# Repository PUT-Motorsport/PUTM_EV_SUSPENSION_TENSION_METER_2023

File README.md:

# Suspension Tension Meter

This circuit is supposed to measure uniaxial forces acting on the push-rods and send collected data over the CAN bus.

## Build

1. Clone the repository:
    ```
    git clone --recurse-submodules 'https://github.com/PUT-Motorsport/PUTM_EV_SUSPENSION_TENSION_METER_2023.git'
    ```
1. Import the project into the CubeIDE.
1. Temporarily rename `main.cpp` to `main.c`.
1. Run the Device Configuration Tool to update the code.
1. Rename `main.c` back to `main.cpp`.

## Firmware

The [Adafruit library](https://github.com/adafruit/Adafruit_NAU7802) and [this project](https://github.com/alex7709/ECE4180F19_CAN_Project) have been used as a reference for writing the driver for the NAU7802.

## Hardware

- [STM32L4P5RET6](https://www.st.com/resource/en/datasheet/stm32l4p5ae.pdf)
- [NAU7802 24-bit ADC](https://www.nuvoton.com/resource-files/NAU7802%20Data%20Sheet%20V1.7.pdf)
- [EMS20 Shear-web Load Cell](https://www.memidos.com/wp-content/uploads/2022/09/EMS20_en.pdf)

## License

    Copyright 2022 Ignacy Kajdan
    
    Licensed under the Apache License, Version 2.0 (the "License");
    you may not use this file except in compliance with the License.
    You may obtain a copy of the License at
    
      https://www.apache.org/licenses/LICENSE-2.0
    
    Unless required by applicable law or agreed to in writing, software
    distributed under the License is distributed on an "AS IS" BASIS,
    WITHOUT WARRANTIES OR CONDITIONS OF ANY KIND, either express or implied.
    See the License for the specific language governing permissions and
    limitations under the License.

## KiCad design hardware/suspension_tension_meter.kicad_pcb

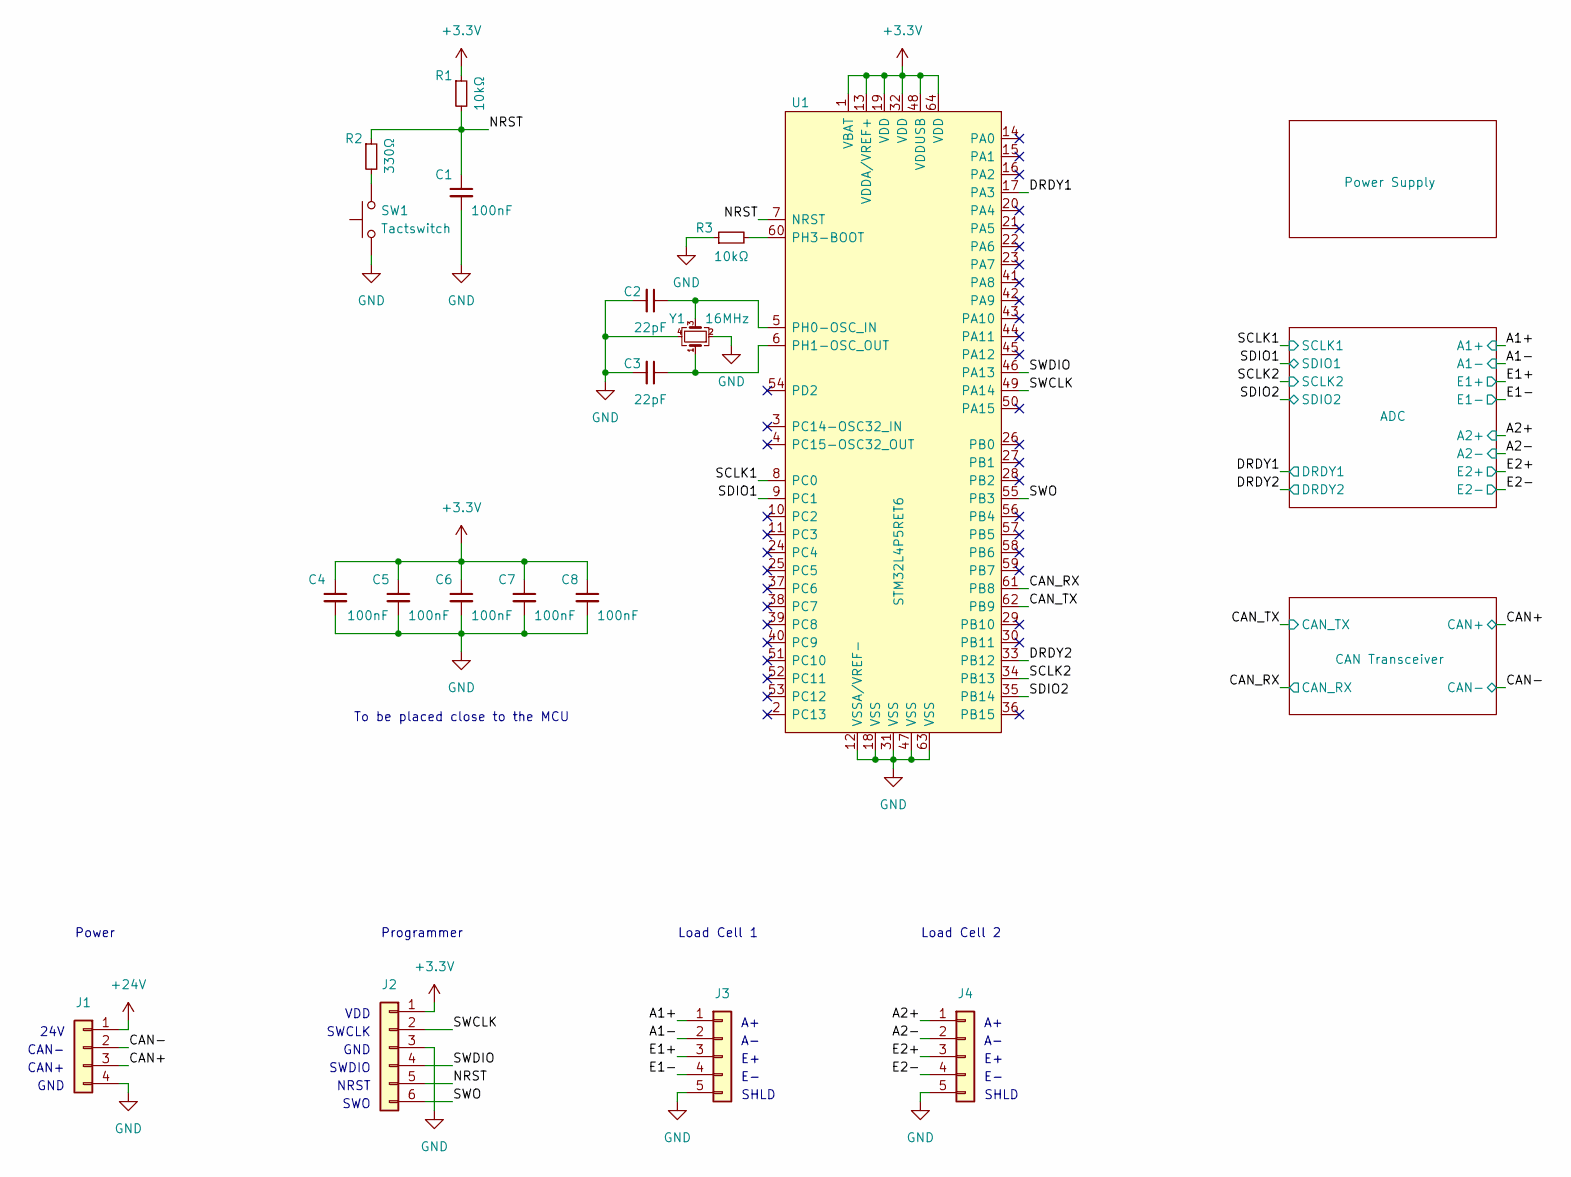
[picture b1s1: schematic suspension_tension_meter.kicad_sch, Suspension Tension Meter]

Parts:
C1, C4, C5, C6, C7, C8: 100nF; C_0603_1608Metric
C2, C3: 22pF; C_0603_1608Metric
J1: Conn_01x04; SolderWire-0.25sqmm_1x04_P4.2mm_D0.65mm_OD1.7mm_Relief
J2: Conn_01x06; PinHeader_1x06_P2.54mm_Vertical
J3, J4: Conn_01x04; Molex_PicoBlade_53048-0510_1x05_P1.25mm_Horizontal
R1, R3: 10kΩ; R_0603_1608Metric
R2: 330Ω; R_0603_1608Metric
SW1: Tactswitch; SW_SPST_PTS645
U1: STM32L4P5RET6; LQFP-64_10x10mm_P0.5mm
Y1: 16MHz; Crystal_SMD_3225-4Pin_3.2x2.5mm

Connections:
+3.3V: C4.1, C5.1, C6.1, C7.1, C8.1, J2.1, J3.3, J4.3, R1.1, U1.1 (VBAT), U1.13 (VDDA/VREF+), U1.19 (VDD), U1.32 (VDD), U1.48 (VDDUSB), U1.64 (VDD); also elsewhere on the board
+24V: J1.1; also elsewhere on the board
/A1+: J3.1; also elsewhere on the board
/A1-: J3.2; also elsewhere on the board
/A2+: J4.1; also elsewhere on the board
/A2-: J4.2; also elsewhere on the board
/CAN+: J1.3; also elsewhere on the board
/CAN-: J1.2; also elsewhere on the board
/CAN_RX: U1.61 (PB8); also elsewhere on the board
/CAN_TX: U1.62 (PB9); also elsewhere on the board
/DRDY1: U1.17 (PA3); also elsewhere on the board
/DRDY2: U1.33 (PB12); also elsewhere on the board
/NRST: C1.1, J2.5, R1.2, R2.1, U1.7 (NRST)
/SCLK1: U1.8 (PC0); also elsewhere on the board
/SCLK2: U1.34 (PB13); also elsewhere on the board
/SDIO1: U1.9 (PC1); also elsewhere on the board
/SDIO2: U1.35 (PB14); also elsewhere on the board
/SWCLK: J2.2, U1.49 (PA14)
/SWDIO: J2.4, U1.46 (PA13)
/SWO: J2.6, U1.55 (PB3)
GND: C1.2, C2.2, C3.2, C4.2, C5.2, C6.2, C7.2, C8.2, J1.4, J2.3, J3.4, J3.5, J4.4, J4.5, R3.1, SW1.1, U1.12 (VSSA/VREF-), U1.18 (VSS), U1.31 (VSS), U1.47 (VSS), U1.63 (VSS), Y1.2, Y1.4; also elsewhere on the board
unnamed: R2.2, SW1.2
unnamed: C2.1, U1.5 (PH0-OSC_IN), Y1.3
unnamed: C3.1, U1.6 (PH1-OSC_OUT), Y1.1
unnamed: R3.2, U1.60 (PH3-BOOT)

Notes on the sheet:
GND
Power
SHLD
To be placed close to the MCU
Load Cell 2
SWCLK
CAN+
NRST
SWO
SHLD
Load Cell 1
CAN-
VDD
Programmer
SWDIO
24V

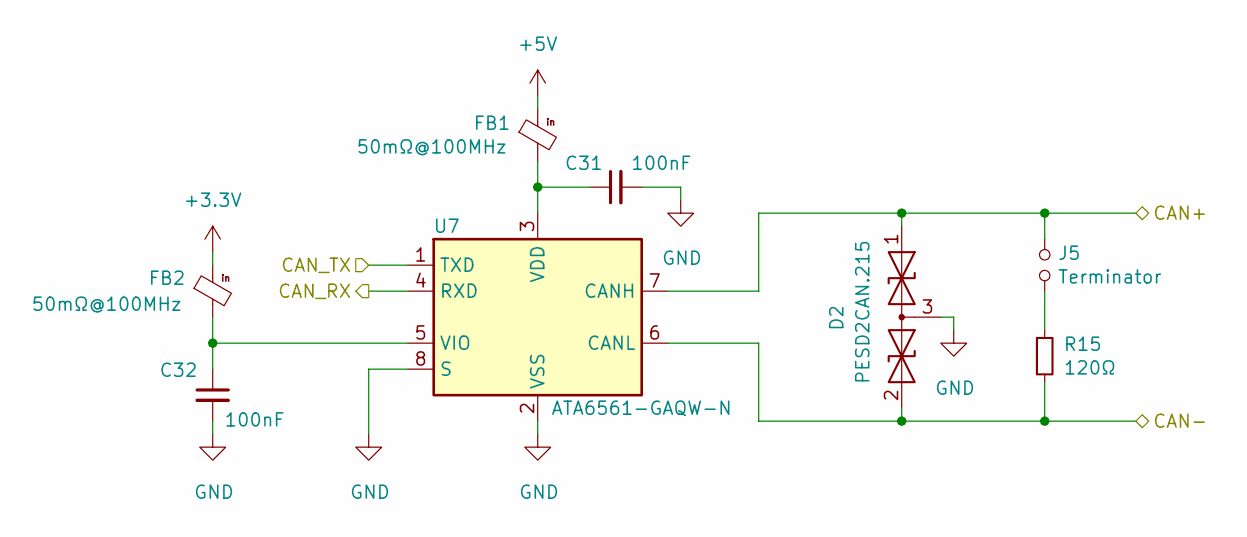
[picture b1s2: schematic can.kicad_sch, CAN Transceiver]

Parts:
C31, C32: 100nF; C_0603_1608Metric
D2: PESD2CAN.215; SOT-23
FB1, FB2: 50mΩ@100MHz; L_1206_3216Metric
J5: Terminator; PinHeader_1x02_P2.54mm_Vertical
R15: 120Ω; R_0603_1608Metric
U7: ATA6561-GAQW-N; SOIC-8_3.9x4.9mm_P1.27mm

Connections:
+3.3V: FB2.1; also elsewhere on the board
+5V: FB1.1; also elsewhere on the board
/CAN+: D2.1 (A1), J5.1, U7.7 (CANH); also elsewhere on the board
/CAN-: D2.2 (A2), R15.2, U7.6 (CANL); also elsewhere on the board
/CAN_RX: U7.4 (RXD); also elsewhere on the board
/CAN_TX: U7.1 (TXD); also elsewhere on the board
GND: C31.2, C32.2, D2.3 (common), U7.2 (VSS), U7.8 (S); also elsewhere on the board
unnamed: J5.2, R15.1
unnamed: C31.1, FB1.2, U7.3 (VDD)
unnamed: C32.1, FB2.2, U7.5 (VIO)

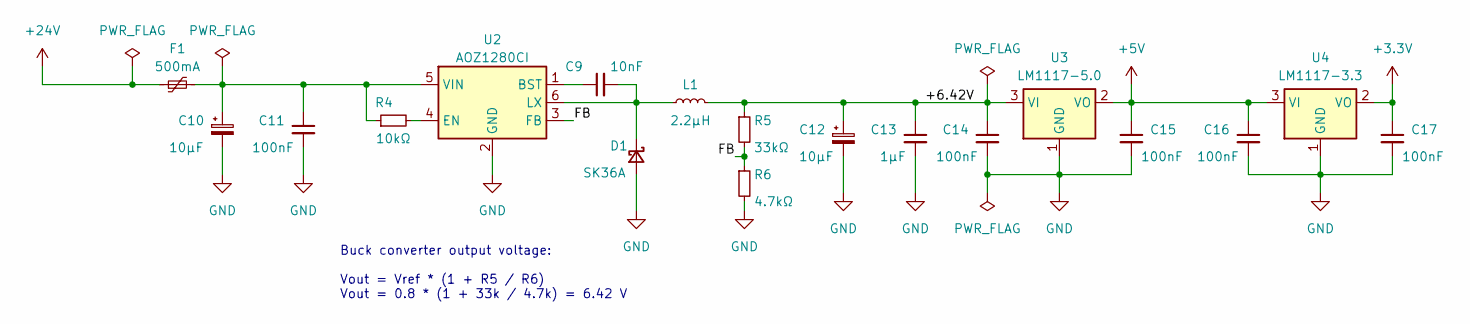
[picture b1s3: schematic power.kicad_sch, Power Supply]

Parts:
C9: 10nF; C_0603_1608Metric
C10, C12: 10μF; CP_Elec_6.3x5.4
C11, C14, C15, C16, C17: 100nF; C_0603_1608Metric
C13: 1μF; C_0603_1608Metric
D1: SK36A; D_SMA
F1: 500mA; Fuse_0805_2012Metric
L1: 2.2μH; L_Bourns-SRN4018
R4: 10kΩ; R_0603_1608Metric
R5: 33kΩ; R_0603_1608Metric
R6: 4.7kΩ; R_0603_1608Metric
U2: AOZ1280CI; SOT-23-6
U3: LM1117-5.0; SOT-223-3_TabPin2
U4: LM1117-3.3; SOT-223-3_TabPin2

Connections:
+3.3V: C17.1, U4.2 (VO); also elsewhere on the board
+5V: C15.1, C16.1, U3.2 (VO), U4.3 (VI); also elsewhere on the board
+24V: F1.1; also elsewhere on the board
/Power Supply/+6.42V: C12.1, C13.1, C14.1, L1.2, R5.1, U3.3 (VI)
/Power Supply/FB: R5.2, R6.1, U2.3 (FB)
GND: C10.2, C11.2, C12.2, C13.2, C14.2, C15.2, C16.2, C17.2, D1.2 (A), R6.2, U2.2 (GND), U3.1 (GND), U4.1 (GND); also elsewhere on the board
unnamed: C10.1, C11.1, F1.2, R4.1, U2.5 (VIN)
unnamed: C9.2, D1.1 (K), L1.1, U2.6 (LX)
unnamed: C9.1, U2.1 (BST)
unnamed: R4.2, U2.4 (EN)

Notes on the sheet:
Buck converter output voltage: Vout = Vref * (1 + R5 / R6) Vout = 0.8 * (1 + 33k / 4.7k) = 6.42 V

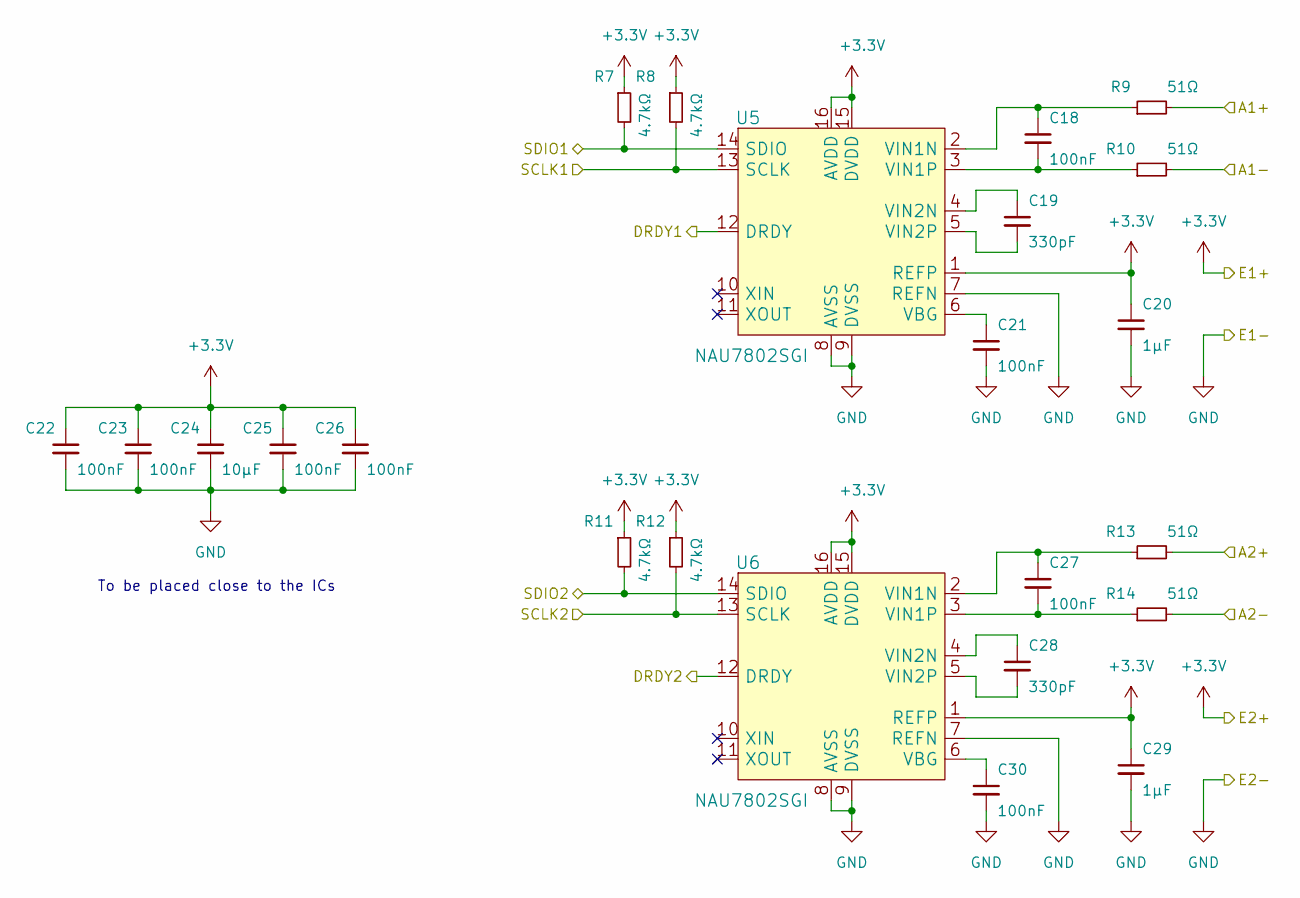
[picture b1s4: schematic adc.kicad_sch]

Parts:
C18, C21, C22, C23, C25, C26, C27, C30: 100nF; C_0603_1608Metric
C19, C28: 330pF; C_0603_1608Metric
C20, C29: 1μF; C_0603_1608Metric
C24: 10μF; C_0603_1608Metric
R7, R8, R11, R12: 4.7kΩ; R_0603_1608Metric
R9, R10, R13, R14: 51Ω; R_0603_1608Metric
U5, U6: NAU7802SGI; SOIC-16_3.9x9.9mm_P1.27mm

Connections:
+3.3V: C20.1, C22.1, C23.1, C24.1, C25.1, C26.1, C29.1, R7.1, R8.1, R11.1, R12.1, U5.1 (REFP), U5.15 (DVDD), U5.16 (AVDD), U6.1 (REFP), U6.15 (DVDD), U6.16 (AVDD); also elsewhere on the board
/A1+: R9.2; also elsewhere on the board
/A1-: R10.2; also elsewhere on the board
/A2+: R13.2; also elsewhere on the board
/A2-: R14.2; also elsewhere on the board
/DRDY1: U5.12 (DRDY); also elsewhere on the board
/DRDY2: U6.12 (DRDY); also elsewhere on the board
/SCLK1: R8.2, U5.13 (SCLK); also elsewhere on the board
/SCLK2: R12.2, U6.13 (SCLK); also elsewhere on the board
/SDIO1: R7.2, U5.14 (SDIO); also elsewhere on the board
/SDIO2: R11.2, U6.14 (SDIO); also elsewhere on the board
GND: C20.2, C21.2, C22.2, C23.2, C24.2, C25.2, C26.2, C29.2, C30.2, U5.7 (REFN), U5.8 (AVSS), U5.9 (DVSS), U6.7 (REFN), U6.8 (AVSS), U6.9 (DVSS); also elsewhere on the board
unnamed: C21.1, U5.6 (VBG)
unnamed: C18.1, R9.1, U5.2 (VIN1N)
unnamed: C18.2, R10.1, U5.3 (VIN1P)
unnamed: C19.1, U5.4 (VIN2N)
unnamed: C19.2, U5.5 (VIN2P)
unnamed: C30.1, U6.6 (VBG)
unnamed: C27.1, R13.1, U6.2 (VIN1N)
unnamed: C27.2, R14.1, U6.3 (VIN1P)
unnamed: C28.1, U6.4 (VIN2N)
unnamed: C28.2, U6.5 (VIN2P)

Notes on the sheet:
To be placed close to the ICs

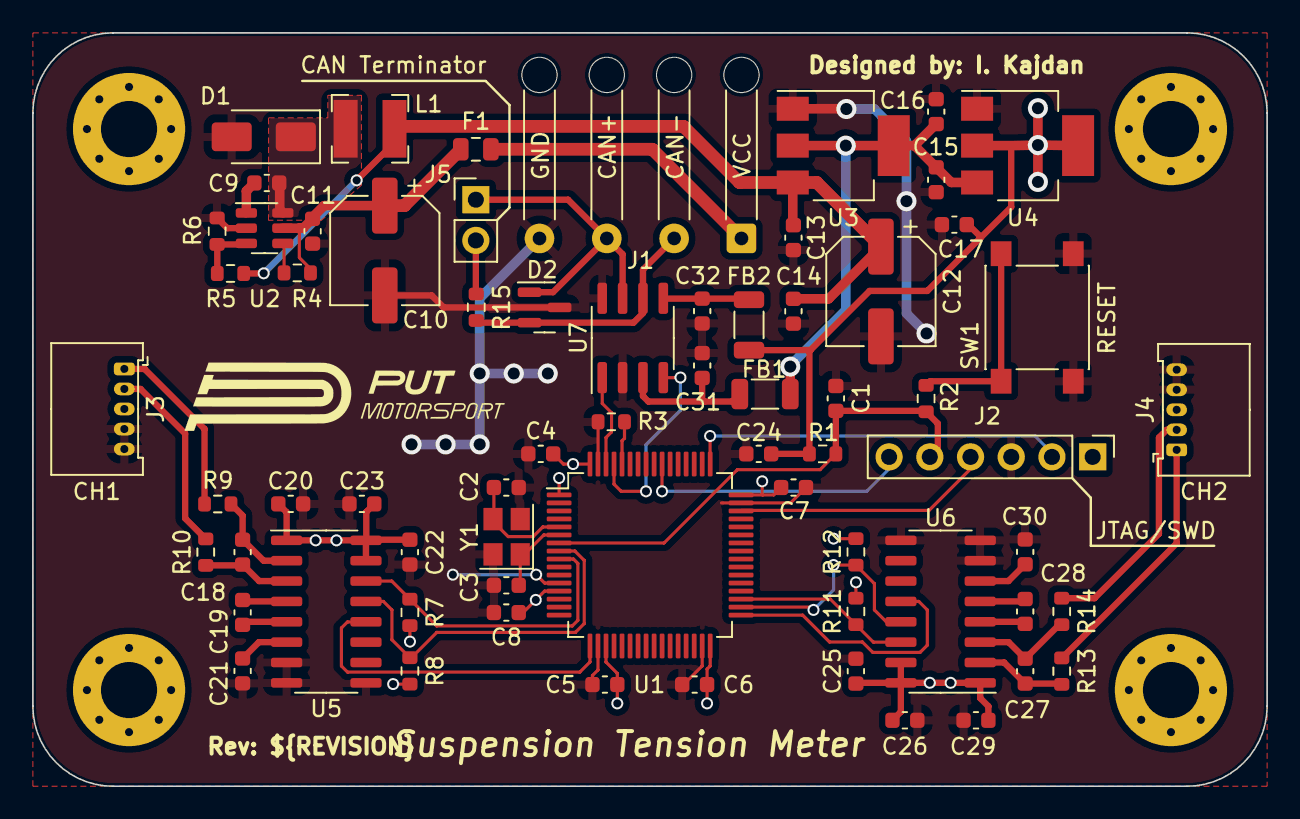
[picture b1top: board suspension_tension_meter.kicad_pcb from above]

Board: 2 copper layers, 77.0 x 47.0 mm, 67 parts (0 on the bottom side), 45 nets.

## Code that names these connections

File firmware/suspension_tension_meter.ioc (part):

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Mcu.Name=STM32L4P5R(G-E)Tx
Mcu.Package=LQFP64
Mcu.UserName=STM32L4P5RETx
PA13\ (JTMS/SWDIO).GPIOParameters=GPIO_Label
PA13\ (JTMS/SWDIO).GPIO_Label=SWDIO
PA13\ (JTMS/SWDIO).Signal=SYS_JTMS-SWDIO
PA14\ (JTCK/SWCLK).GPIOParameters=GPIO_Label
PA14\ (JTCK/SWCLK).GPIO_Label=SWCLK
PA14\ (JTCK/SWCLK).Signal=SYS_JTCK-SWCLK
PA3.GPIOParameters=GPIO_Label
PA3.GPIO_Label=DRDY1
PA3.Signal=GPXTI3
PB12.GPIOParameters=GPIO_Label
PB12.GPIO_Label=DRDY2
PB12.Signal=GPXTI12
PB13.GPIOParameters=GPIO_Label
PB13.GPIO_Label=SCLK2
PB13.Mode=I2C
PB13.Signal=I2C2_SCL
PB14.GPIOParameters=GPIO_Label
PB14.GPIO_Label=SDIO2
PB14.Mode=I2C
PB14.Signal=I2C2_SDA
PB3\ (JTDO/TRACESWO).GPIOParameters=GPIO_Label
PB3\ (JTDO/TRACESWO).GPIO_Label=SWO
PB3\ (JTDO/TRACESWO).Signal=SYS_JTDO-SWO
PB8.GPIOParameters=GPIO_Label
PB8.GPIO_Label=CAN_RX
PB8.Mode=CAN_Activate
PB8.Signal=CAN1_RX
PB9.GPIOParameters=GPIO_Label
PB9.GPIO_Label=CAN_TX
PB9.Mode=CAN_Activate
PB9.Signal=CAN1_TX
PC0.GPIOParameters=GPIO_Label
PC0.GPIO_Label=SCLK1
PC0.Mode=I2C
PC0.Signal=I2C3_SCL
PC1.GPIOParameters=GPIO_Label
PC1.GPIO_Label=SDIO1
PC1.Mode=I2C
PC1.Signal=I2C3_SDA
PH0-OSC_IN\ (PH0).Mode=HSE-External-Oscillator
PH0-OSC_IN\ (PH0).Signal=RCC_OSC_IN
PH1-OSC_OUT\ (PH1).Mode=HSE-External-Oscillator
PH1-OSC_OUT\ (PH1).Signal=RCC_OSC_OUT
RCC.HSE_VALUE=8000000
RCC.SYSCLKFreq_VALUE=64000000
RCC.SYSCLKSource=RCC_SYSCLKSOURCE_PLLCLK
board=custom

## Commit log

2022-11-21 Improve the CAN transceiver circuit
2022-11-21 Add a low-pass filter to the analog circuit supply
2022-11-23 Add readme and license files
2022-11-29 Improve power delivery sheet:
    - Move power connector to the main sheet
    - Use PTC fuse
2022-11-30 Refactor the main sheet
    - Replace screw connectors with a goldpin header
    - Add reset button
    - Add SWD debugger header
2022-12-04 Add ADC circuit
2022-12-04 Connect each ADC to a separate I2C bus
2022-12-05 Assign footprints to symbols
2022-12-06 Use more efficient buck converter
2022-12-10 Arrange footprints
2022-12-11 Make the PCB more compact
2022-12-11 Apply PUTM branding
2022-12-17 Use smaller logo
2022-12-18 Miscellaneous changes
    - Use THT connectors
    - Adjust ADC circuit according to the datasheet
2022-12-19 Route PCB tracks
2022-12-19 Add PCB render to the README
2022-12-22 Move input capacitor closer to the converter IC
2022-12-22 Improve routing around the buck converter
2022-12-28 Release v1.0.0
2023-03-13 Port the project to KiCad 7
2023-03-19 Create a new Cube project
2023-03-19 Configure clocks
2023-04-01 Implement NAU7802 driver
2023-04-02 Add a 3D model for the connectors
2023-04-02 Add CAN communication
2023-04-02 Update the PCB render
2023-05-07 Apply KiCad template to the project
2023-05-08 Assign labels to SWD pins
2024-04-16 Added new, debugged power supply, but the old one is still there, just in case
2024-05-14 finalna wersja zasilania, zatwierdzona
